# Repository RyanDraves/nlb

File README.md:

# NLB
Personal projects and monorepo adventures.

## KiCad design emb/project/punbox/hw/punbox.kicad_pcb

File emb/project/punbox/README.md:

# Punbox

A small USB-powered box: tell a pun, press the button on top, and a
"buh dum tsss" plays through the speakers.

## Development hardware

- Raspberry Pi Pico (RP2040)
- [Waveshare Pico-Audio](https://www.waveshare.com/pico-audio.htm) (original
  revision): PCM5101A I2S DAC + APA2068 speaker amp
- 8Ω 2W speakers
- Momentary pushbutton

### Pinout

| Signal | GPIO | Notes |
| --- | --- | --- |
| I2S DIN | GP26 | Wired by the Pico-Audio module |
| I2S BCK | GP27 | Wired by the Pico-Audio module |
| I2S LRCK | GP28 | Wired by the Pico-Audio module |
| Button | GP6 | Active-low against an internal pull-up; other leg to GND |

## Architecture

- `logic.{hpp,cc}`: `PunboxLogic`, the platform-free core (button debounce →
  clip playback). Unit-tested in `logic_test.cc`.
- `punbox.cc`: the buffham `Punbox` handlers (`play_sound`, `get_state`) plus
  `tick()`, a buffham `svr_method` the main loop calls to poll the button.
- `//emb/yaal:audio`: PIO + DMA I2S driver; clips stream from flash with no
  CPU involvement.
- `:rimshot`: the sound clip, embedded at build time by
  `//nlb/wav:wav2cc` as 16-bit stereo PCM (see `wav_cc_library`).

## Sound clip

`data/rimshot.wav`:

- Source: ["Ba Dum Tss! (classic edition)" by DJczyszy on Freesound](https://freesound.org/people/DJczyszy/sounds/431811/)
- License: CC0 1.0

## Flashing

Provision a fresh Pico (BOOTSEL mode) with the bootloader and base image:

```sh
bazel run //emb/project/bootloader:provision_pico
```

Then flash (and re-flash) punbox over USB serial:

```sh
bazel run //emb/project/punbox:punbox_flash
```

## Hardware smoke test

1. `bazel test //emb/project/punbox:hil_test` — pings the board, triggers
   playback, and verifies the state; the rimshot should play through the
   speakers (the target is tagged `manual`, so CI skips it)
2. Press the physical button — the rimshot should play again
3. Re-run `:hil_test` (or use `:shell` and `client.get_state()`) —
   `press_count` should reflect both the RPC triggers and the physical press

For interactive poking, `bazel run //emb/project/punbox:shell` opens an
IPython shell with `client` connected over USB serial.

## Tests

```sh
bazel test //emb/project/punbox/...   # unit + host integration tests
bazel test //nlb/wav/...              # clip embedding tool
```

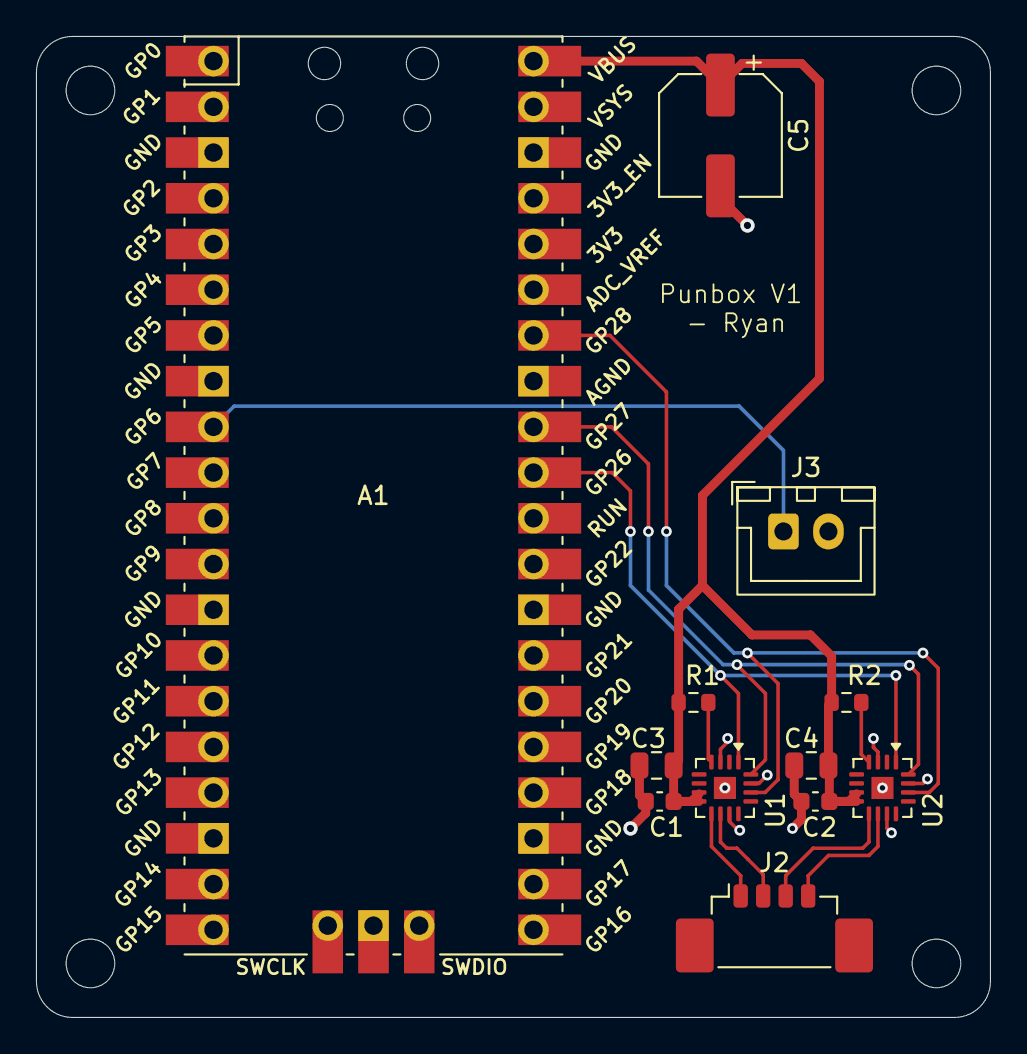
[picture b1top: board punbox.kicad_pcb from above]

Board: 2 copper layers, 53.0 x 54.5 mm, 12 parts (0 on the bottom side), 12 nets.

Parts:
A1: Pico; RPi_Pico_SMD_TH
C1, C2: 100nF; C_0603_1608Metric
C3, C4: 10uF; C_0805_2012Metric
C5: 100uF; CP_Elec_6.3x5.4
J2: Speakers; Molex_PicoBlade_53398-0471_1x04-1MP_P1.25mm_Vertical
J3: Button; JST_XH_B2B-XH-A_1x02_P2.50mm_Vertical
R1: 100k; R_0603_1608Metric
R2: 390k; R_0603_1608Metric
U1, U2: MAX98357A; TQFN-16-1EP_3x3mm_P0.5mm_EP1.23x1.23mm

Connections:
+5V: A1.40, C1.1, C2.1, C3.1, C4.1, C5.1, R1.2, R2.2, U1.7, U1.8, U2.7, U2.8
BUTTON: A1.9, J3.1
GND: A1.3, A1.8, A1.13, A1.18, A1.23, A1.28, A1.38, A1.42, C1.2, C2.2, C3.2, C4.2, C5.2, J3.2, U1.3, U1.11, U1.15, U1.17, U2.3, U2.11, U2.15, U2.17
I2S_BCLK: A1.32, U1.16, U2.16
I2S_DIN: A1.31, U1.1, U2.1
I2S_LRCLK: A1.34, U1.14, U2.14
unnamed: J2.1, U1.9
unnamed: J2.2, U1.10
unnamed: J2.3, U2.9
unnamed: J2.4, U2.10
U1_SD_MODE: R1.1, U1.4
U2_SD_MODE: R2.1, U2.4

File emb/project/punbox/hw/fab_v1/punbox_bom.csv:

Comment,Designator,Footprint,LCSC Part #
100k,R1,R_0603_1608Metric,C25803
100nF,"C1,C2",C_0603_1608Metric,C14663
100uF,C5,CP_Elec_6.3x5.4,C970684
10uF,"C3,C4",C_0805_2012Metric,C15850
390k,R2,R_0603_1608Metric,C23150
MAX98357A,"U1,U2",TQFN-16-1EP_3x3mm_P0.5mm_EP1.23x1.23mm,C910544
Speakers,J2,Molex_PicoBlade_53398-0471_1x04-1MP_P1.25mm_Vertical,C17617036

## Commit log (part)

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2026-02-21 default setec server arg
2026-03-07 fork bubbles and make things more usable
2026-03-07 Rewrite nlb_tailscale in Go (#212)
    As a first foray into writing some Go and using Tailscale libraries
    directly, rewrite my Tailscale CLI extension to be in Go. This has a few
    advantages:
    - It produces a simple binary that's much easier to distribute
    - I can hook into the Tailscale API/abstractions closer to list
    Taildrop-compatible devices
2026-03-29 update tailscale sidecar
2026-03-29 fix container rename
2026-03-29 more fixes
2026-03-29 Standardize compose files (#214)
    I've been patching files in an ad-hoc manner for a bit. This PR gets a
    few services up-to-date and adopts a more standard format for what
    should be in each compose file.
2026-03-29 update setec
2026-03-30 Update setec to latest upstream (#215)
    Tailscale maintainers patched what I needed a fork for in setec; update
    to latest
2026-05-03 Add setup alias
2026-05-03 fix macos openjdk install
2026-05-03 Fix MacOS OpenJDK install (#217)
    what a fun OS
2026-05-27 Add latex setup (#232)
    Some setup scripting for getting Latex installed. Takes five years to
    install so keep things pretty manual for now.
2026-05-27 Setup Renovate and Dependabot
2026-05-27 Setup Renovate and Dependabot (#233)
    Setup Dependabot and Renovate for automated dependency management. It
    might even work, who knows.
    Closes #228
    Closes #229
2026-05-27 Bump pillow from 11.1.0 to 12.2.0
    Bumps [pillow](https://github.com/python-pillow/Pillow) from 11.1.0 to 12.2.0.
    - [Release notes](https://github.com/python-pillow/Pillow/releases)
    - [Changelog](https://github.com/python-pillow/Pillow/blob/main/CHANGES.rst)
    - [Commits](https://github.com/python-pillow/Pillow/compare/11.1.0...12.2.0)
    ---
    updated-dependencies:
2026-05-27 Bump python-multipart from 0.0.20 to 0.0.27
    Bumps [python-multipart](https://github.com/Kludex/python-multipart) from 0.0.20 to 0.0.27.
    - [Release notes](https://github.com/Kludex/python-multipart/releases)
    - [Changelog](https://github.com/Kludex/python-multipart/blob/main/CHANGELOG.md)
    - [Commits](https://github.com/Kludex/python-multipart/compare/0.0.20...0.0.27)
    ---
    updated-dependencies:
2026-05-27 Bump mako from 1.3.9 to 1.3.12
    Bumps [mako](https://github.com/sqlalchemy/mako) from 1.3.9 to 1.3.12.
    - [Release notes](https://github.com/sqlalchemy/mako/releases)
    - [Changelog](https://github.com/sqlalchemy/mako/blob/main/CHANGES)
    - [Commits](https://github.com/sqlalchemy/mako/commits)
    ---
    updated-dependencies:
2026-05-27 Bump idna from 3.10 to 3.15
    Bumps [idna](https://github.com/kjd/idna) from 3.10 to 3.15.
    - [Release notes](https://github.com/kjd/idna/releases)
    - [Changelog](https://github.com/kjd/idna/blob/master/HISTORY.md)
    - [Commits](https://github.com/kjd/idna/compare/v3.10...v3.15)
    ---
    updated-dependencies:
2026-05-27 don't need dependabot config I guess
2026-05-27 Fix renovate config
2026-05-27 Fix Renovate Config (#245)
    Apparently we're still just in the hallucination phase of AI. Cool.
2026-05-28 update pnpm management
2026-05-28 Update dependency vitest to v1.6.1 [SECURITY] (#248)
    > ℹ️ **Note**
    >
    > This PR body was truncated due to platform limits.
    This PR contains the following updates:
    | Package | Change |
    [Age](https://docs.renovatebot.com/merge-confidence/) |
2026-05-28 Update dependency next to v15.5.18 [SECURITY]
2026-05-28 Update dependency next to v15.5.18 [SECURITY] (#246)
    > ℹ️ **Note**
    >
    > This PR body was truncated due to platform limits.
    This PR contains the following updates:
    | Package | Change |
    [Age](https://docs.renovatebot.com/merge-confidence/) |
2026-05-28 Update dependency cryptography to v46.0.7 [SECURITY]
2026-05-28 Update dependency mako to v1.3.12 [SECURITY]
2026-05-28 Update dependency python-multipart to v0.0.27 [SECURITY]
2026-05-28 Update dependency fonttools to v4.60.2 [SECURITY]
2026-05-28 Update dependency idna to v3.15 [SECURITY]
2026-05-28 Update dependency mcp to v1.23.0 [SECURITY]
2026-05-28 Update dependency postcss to v8.5.10 [SECURITY]
2026-05-28 Update dependency pygments to v2.20.0 [SECURITY]
2026-05-28 Update dependency requests to v2.33.0 [SECURITY]
2026-05-28 Update dependency starlette to v0.49.1 [SECURITY]
2026-05-28 Update dependency postcss to v8.5.10 [SECURITY] (#247)
    This PR contains the following updates:
    | Package | Change |
    [Age](https://docs.renovatebot.com/merge-confidence/) |
    [Confidence](https://docs.renovatebot.com/merge-confidence/) |
    |---|---|---|---|
    | [postcss](https://postcss.org/)
2026-05-28 Fix Python Renovation
2026-05-28 Update dependency fastmcp to v3 [SECURITY]
2026-05-28 Update dependency pillow to v12 [SECURITY]
2026-05-28 Update dependency pip to v26 [SECURITY]
2026-05-28 Update python security updates
2026-05-28 Regenerate Python lockfile and gazelle manifest
2026-05-28 Update python security updates (major) (#271)
    This PR contains the following updates:
    | Package | Change |
    [Age](https://docs.renovatebot.com/merge-confidence/) |
    [Confidence](https://docs.renovatebot.com/merge-confidence/) |
    |---|---|---|---|
    | [OpenAI](https://redirect.github.com/openai/openai-python) |
2026-05-28 Bump Python deps manually
2026-05-28 try pip downdate
2026-05-28 fixes?
2026-05-28 Fastmcp bump
2026-05-28 Pygments bump
2026-05-28 Pytest bump
2026-05-28 Pip bump
2026-05-28 Bump rules_python
2026-05-28 Bump Python deps manually (#273)
    Create the version bump manually for the deps we specify that got closed
    when Renovate opened 20 PRs. Renovate won't suggest these bumps unless
    we do it manually.
2026-05-28 Bump marshmallow from 4.0.0 to 4.1.2
    Bumps [marshmallow](https://github.com/marshmallow-code/marshmallow) from 4.0.0 to 4.1.2.
    - [Changelog](https://github.com/marshmallow-code/marshmallow/blob/dev/CHANGELOG.rst)
    - [Commits](https://github.com/marshmallow-code/marshmallow/compare/4.0.0...4.1.2)
    ---
    updated-dependencies:
    - dependency-name: marshmallow
2026-05-28 macos setup fixes
2026-05-28 Bump cryptography from 46.0.0 to 46.0.7
    Bumps [cryptography](https://github.com/pyca/cryptography) from 46.0.0 to 46.0.7.
    - [Changelog](https://github.com/pyca/cryptography/blob/main/CHANGELOG.rst)
    - [Commits](https://github.com/pyca/cryptography/compare/46.0.0...46.0.7)
    ---
    updated-dependencies:
    - dependency-name: cryptography
2026-05-28 Bump python-dotenv from 1.1.0 to 1.2.2
    Bumps [python-dotenv](https://github.com/theskumar/python-dotenv) from 1.1.0 to 1.2.2.
    - [Release notes](https://github.com/theskumar/python-dotenv/releases)
    - [Changelog](https://github.com/theskumar/python-dotenv/blob/main/CHANGELOG.md)
    - [Commits](https://github.com/theskumar/python-dotenv/compare/v1.1.0...v1.2.2)
    ---
    updated-dependencies:
2026-05-28 dotenv update
2026-05-28 Update node packages
2026-05-28 update manifest
2026-05-28 Migrate config renovate.json
2026-05-29 Migrate Renovate config (#286)
    The Renovate config in this repository needs migrating. Typically this
    is because one or more configuration options you are using have been
    renamed.
    You don't need to merge this PR right away, because Renovate will
    continue to migrate these fields internally each time it runs. But later
    some of these fields may be fully deprecated and the migrations removed.
2026-05-30 cleanup files and remove claude talking to me in the comments
2026-05-30 Blog satellite visualization (#287)
    Create a blog page that visualizes the satellites I've worked on.
    This creation was my first use of the Opus model. It did a wonderful job
    and greatly outperformed the Copilot attempt at this I tried a year ago
    or so. It took quite a few nudges to get things working, but I'm overall
    very impressed with what it was able to achieve.
2026-06-01 Monthly satellite TLE refresh
2026-06-01 update workflow for automated test runs
2026-06-01 remove newlines from the PR body
2026-06-06 Update module charm.land/lipgloss/v2 to v2.0.3 (#296)
    This PR contains the following updates:
    | Package | Change |
    [Age](https://docs.renovatebot.com/merge-confidence/) |
    [Confidence](https://docs.renovatebot.com/merge-confidence/) |
    |---|---|---|---|
    |
2026-06-06 Update module charm.land/bubbletea/v2 to v2.0.7 (#295)
    This PR contains the following updates:
    | Package | Change |
    [Age](https://docs.renovatebot.com/merge-confidence/) |
    [Confidence](https://docs.renovatebot.com/merge-confidence/) |
    |---|---|---|---|
    |
2026-06-10 progress
2026-06-10 libzmq macos support
2026-06-10 Punbox Dev Board (#298)
    Looks like I got _BOARD_ yesterday. *Buh Dum Tsss*
2026-06-10 looking good
2026-06-11 Flash upgrades and USB reconnect logic
2026-06-11 document links
2026-06-11 definition links
2026-06-11 fix references
2026-06-11 rename and completions
2026-06-11 Buffham Editor Support (#303)
    Make a VSCode extension to add rich features to `.bh` files. Works
    pretty good and all Bazel-fied
2026-06-12 renovate fixes
2026-06-12 Update github.com/tailscale/setec digest to 802071d (#288)
    This PR contains the following updates:
    | Package | Type | Update | Change |
    |---|---|---|---|
    |
    [github.com/tailscale/setec](https://redirect.github.com/tailscale/setec)
    | require | digest | `dcd97e4` → `802071d` |
2026-06-12 Tidy Go modules
2026-06-12 Update go security updates (#304)
    This PR contains the following updates:
    | Package | Change |
    [Age](https://docs.renovatebot.com/merge-confidence/) |
    [Confidence](https://docs.renovatebot.com/merge-confidence/) |
    |---|---|---|---|
    |
2026-06-12 Update npm renovate config (#306)
    Make it like Python/Go & ensure package.json updates
2026-06-12 Update npm security updates
2026-06-12 Security bumps to highest version
2026-06-12 Update go security updates to v1.96.2 (#309)
    This PR contains the following updates:
    | Package | Change |
    [Age](https://docs.renovatebot.com/merge-confidence/) |
    [Confidence](https://docs.renovatebot.com/merge-confidence/) |
    |---|---|---|---|
    | [tailscale.com](https://redirect.github.com/tailscale/tailscale) |
2026-06-12 Update npm security updates (#307)
    This PR contains the following updates:
    | Package | Change |
    [Age](https://docs.renovatebot.com/merge-confidence/) |
    [Confidence](https://docs.renovatebot.com/merge-confidence/) | Type |
    Update |
    |---|---|---|---|---|---|
2026-06-12 Update dependency next to v15.5.19 [SECURITY]
2026-06-12 Update dependency next to v15.5.19 [SECURITY] (#313)
    > ℹ️ **Note**
    >
    > This PR body was truncated due to platform limits.
    This PR contains the following updates:
    | Package | Change |
    [Age](https://docs.renovatebot.com/merge-confidence/) |
2026-06-12 Renovate security config fixes
2026-06-12 Renovate security config fixes (#315)
    Letting Opus take this one...
2026-06-13 Update npm dependencies
2026-06-13 Update docker service images
2026-06-15 initial game
2026-06-17 new icons
2026-06-18 Put AI in timeout
2026-06-20 Update github actions
2026-06-30 Update ubuntu Docker tag to noble-20260509.1 (#317)
    This PR contains the following updates:
    | Package | Type | Update | Change |
    |---|---|---|---|
    | ubuntu | final | patch | `noble-20260410` → `noble-20260509.1` |
    ---
    ### Configuration
2026-06-30 Update docker service images (#319)
    > ℹ️ **Note**
    >
    > This PR body was truncated due to platform limits.
    This PR contains the following updates:
    | Package | Update | Change |
    |---|---|---|
2026-06-30 Update go modules to v1.100.0 (#322)
    This PR contains the following updates:
    | Package | Change |
    [Age](https://docs.renovatebot.com/merge-confidence/) |
    [Confidence](https://docs.renovatebot.com/merge-confidence/) |
    |---|---|---|---|
    | [tailscale.com](https://redirect.github.com/tailscale/tailscale) |
